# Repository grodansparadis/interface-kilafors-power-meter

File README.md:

# VSCP interface to Power meter LED's

This is work in progress.

Copyright 2018 [Ake Hedman, Grodans Paradis AB](akhe@grodansparadis.com)

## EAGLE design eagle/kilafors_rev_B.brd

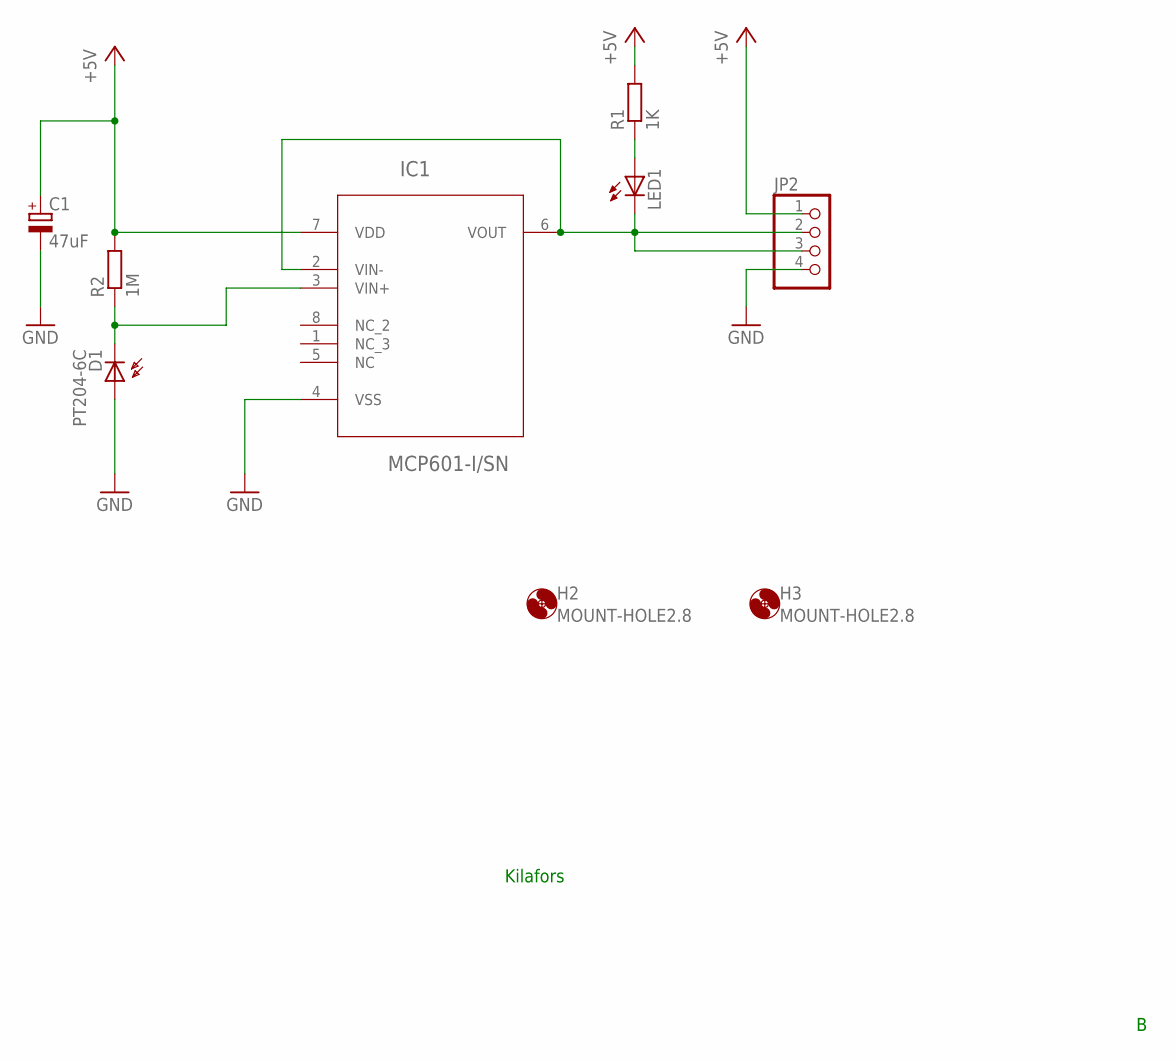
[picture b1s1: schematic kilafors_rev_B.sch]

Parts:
C1: 47uF; E5-5
D1: PT204-6C; BPW32
H2, H3: MOUNT-HOLE2.8; 2,8
IC1: MCP601-I/SN; SOIC127P600X175-8N
JP2: PINHD-1X4; 1X04
LED1: LED3MM
R1: 1K; 0204/5
R2: 1M; 0204/5

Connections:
+5V: C1.+, IC1.7 (VDD), JP2.1, R1.2, R2.2
GND: C1.-, D1.A, IC1.4 (VSS), JP2.4
unnamed: IC1.2 (VIN-), IC1.6 (VOUT), JP2.2, JP2.3, LED1.K (C)
unnamed: D1.K (C), IC1.3 (VIN+), R2.1
unnamed: LED1.A, R1.1

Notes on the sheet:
Kilafors

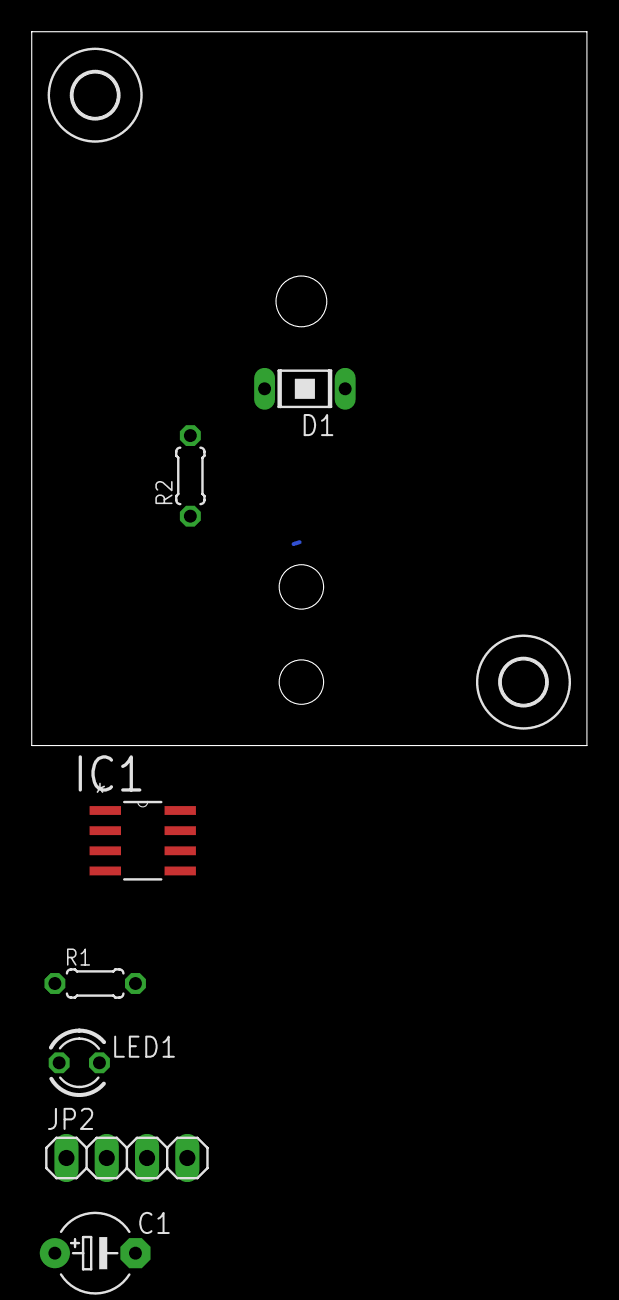
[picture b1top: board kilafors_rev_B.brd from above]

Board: 2 copper layers, 35.0 x 45.0 mm, 9 parts (0 on the bottom side), 5 nets.

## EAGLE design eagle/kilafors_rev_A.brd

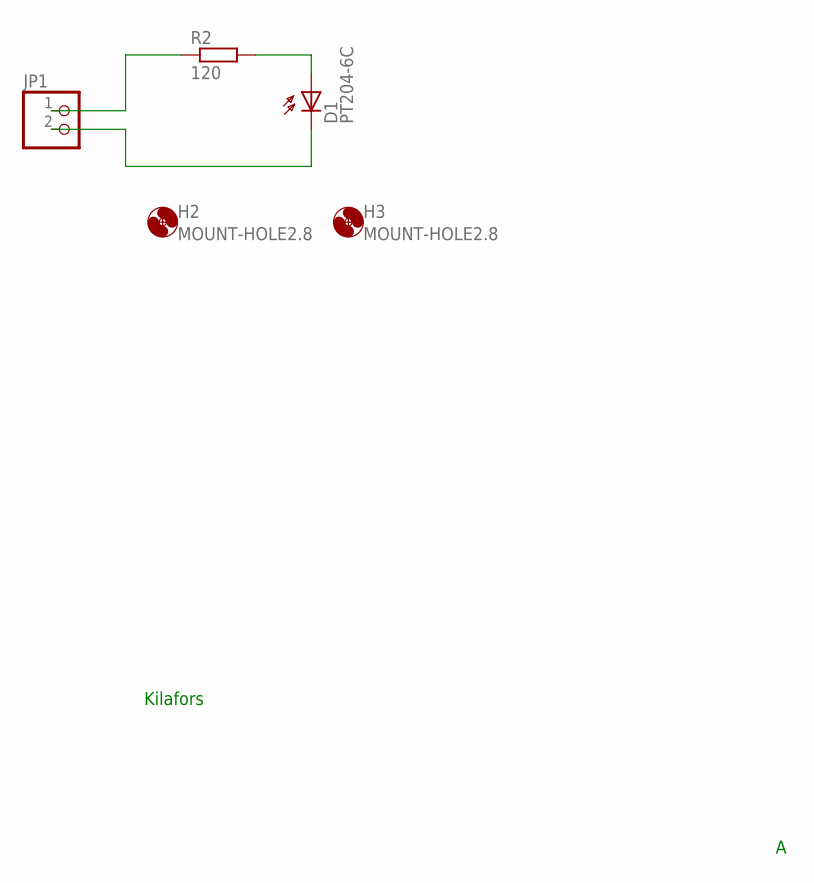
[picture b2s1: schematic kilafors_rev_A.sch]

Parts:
D1: PT204-6C; BPW32
H2, H3: MOUNT-HOLE2.8; 2,8
JP1: PINHD-1X2; 1X02
R2: 120; 0204/5

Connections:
unnamed: D1.A, R2.2
unnamed: JP1.1, R2.1
unnamed: D1.K (C), JP1.2

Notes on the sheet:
Kilafors

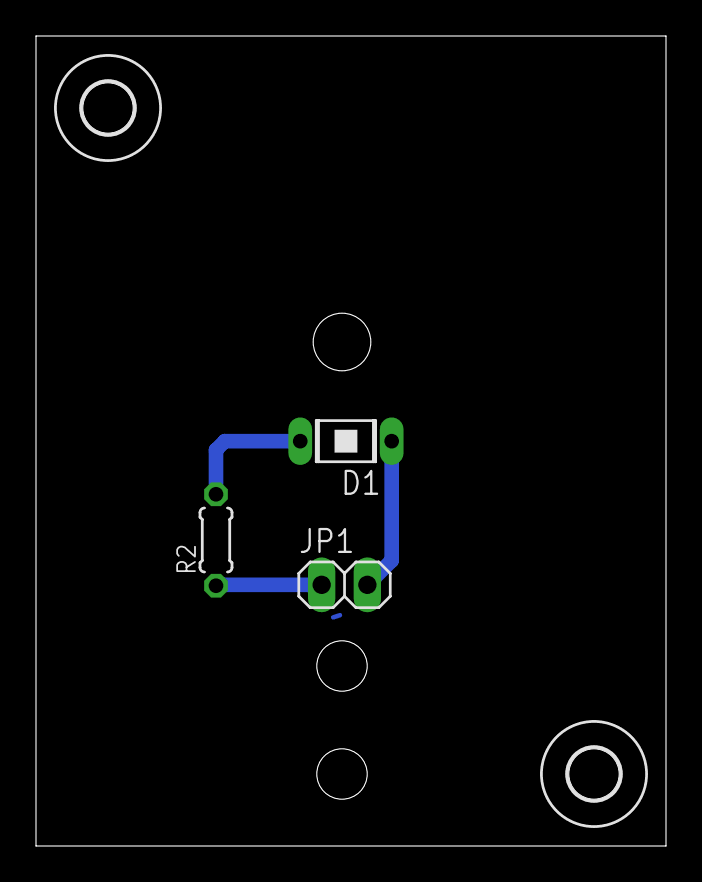
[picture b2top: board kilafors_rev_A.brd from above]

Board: 2 copper layers, 35.0 x 45.0 mm, 5 parts (0 on the bottom side), 3 nets.

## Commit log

2018-11-12 Moved from VSCP hardware
2018-11-12 Updated schematic to an active circuit
2018-11-12 Corrected copyright
